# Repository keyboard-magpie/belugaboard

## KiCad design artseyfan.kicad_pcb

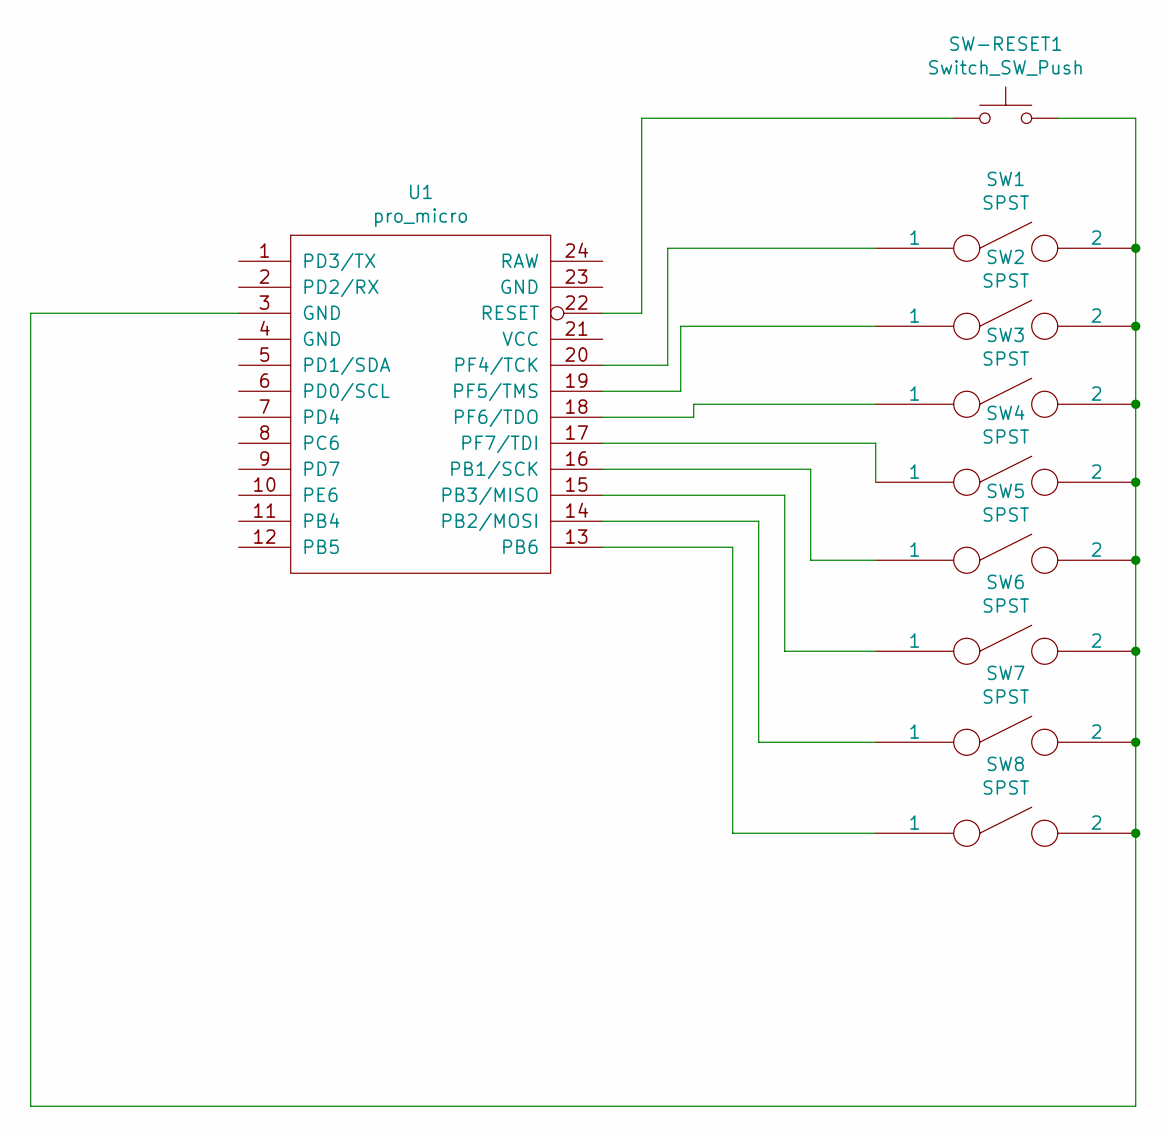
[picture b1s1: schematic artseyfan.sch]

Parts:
SW1, SW2, SW3, SW4, SW5, SW6, SW7, SW8: SPST; MX-Alps-Choc-X-1U-NoLED
SW-RESET1: Switch_SW_Push; reset-button
U1: pro_micro; BOARD_Pro_Micro_Reversed

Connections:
unnamed: SW1.1, U1.20 (PF4/TCK)
unnamed: SW2.1, U1.19 (PF5/TMS)
unnamed: SW3.1, U1.18 (PF6/TDO)
unnamed: SW4.1, U1.17 (PF7/TDI)
unnamed: SW5.1, U1.16 (PB1/SCK)
unnamed: SW6.1, U1.15 (PB3/MISO)
unnamed: SW7.1, U1.14 (PB2/MOSI)
unnamed: SW8.1, U1.13 (PB6)
unnamed: SW-RESET1.1, U1.22 (RESET)
unnamed: SW1.2, SW2.2, SW3.2, SW4.2, SW5.2, SW6.2, SW7.2, SW8.2, SW-RESET1.2, U1.3 (GND)

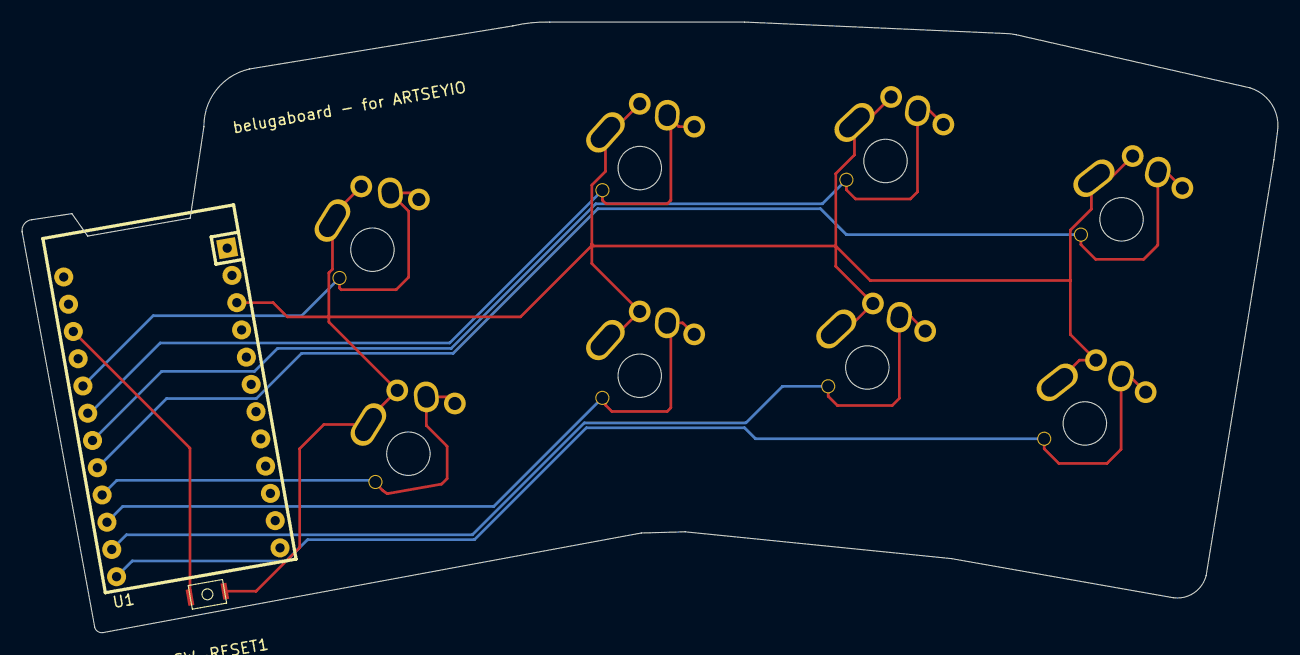
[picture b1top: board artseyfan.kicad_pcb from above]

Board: 2 copper layers, 115.3 x 56.1 mm, 10 parts (0 on the bottom side), 10 nets.
